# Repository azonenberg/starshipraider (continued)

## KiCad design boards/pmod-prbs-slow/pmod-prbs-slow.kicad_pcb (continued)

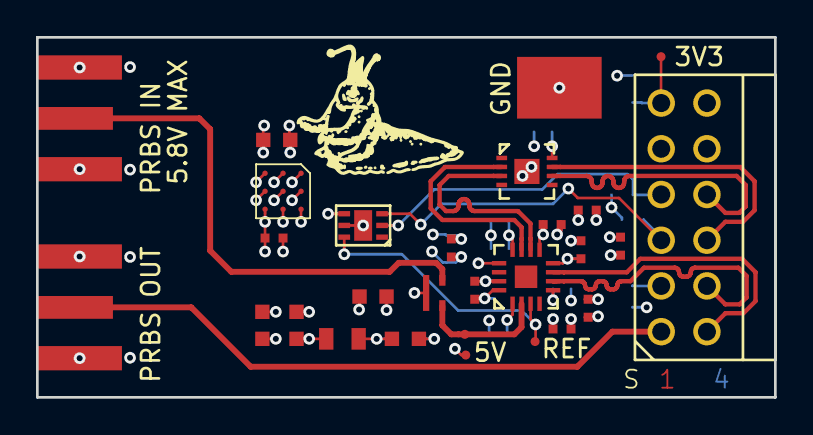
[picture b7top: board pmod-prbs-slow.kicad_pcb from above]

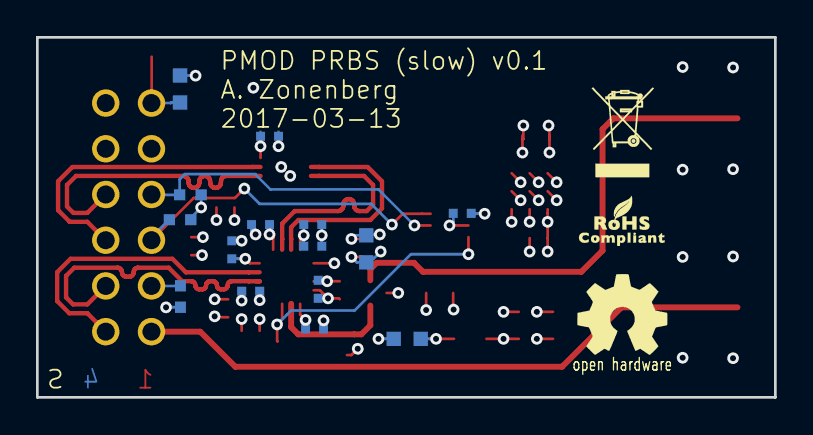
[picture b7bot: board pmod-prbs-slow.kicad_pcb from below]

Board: 4 copper layers, 41.0 x 20.0 mm, 43 parts (15 on the bottom side), 17 nets.

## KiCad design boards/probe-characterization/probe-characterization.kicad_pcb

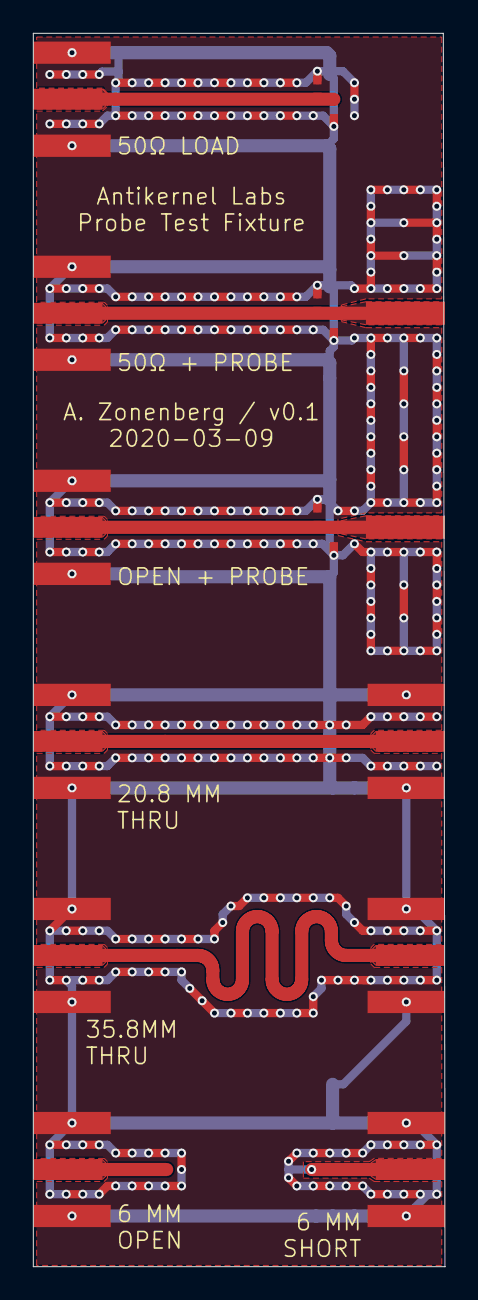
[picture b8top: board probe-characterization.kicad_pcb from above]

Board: 2 copper layers, 25.0 x 74.9 mm, 17 parts (0 on the bottom side), 6 nets.

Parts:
J1, J2, J3, J4, J5, J6, J7, J8, J9: SMA; CONN_SMA_EDGE_SAMTEC_SMA_J_P_H_ST_EM1
J10, J11: PROBE; CONN_MILLMAX_0339_EDGELAUNCH
R1, R2, R4, R5: 100; EIA_0402_RES_NOSILK_FLIPCHIP
R3, R6: DNP; EIA_0402_RES_NOSILK_FLIPCHIP

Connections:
/GND: J1.2, J2.2, J3.2, J4.2, J5.2, J6.2, J7.1, J7.2, J8.2, J9.2, R1.2, R2.2, R3.2, R4.2, R5.2, R6.2
unnamed: J1.1, R1.1, R4.1
unnamed: J4.1, J8.1
unnamed: J5.1, J9.1
unnamed: J2.1, J10.1, R2.1, R5.1
unnamed: J3.1, J11.1, R3.1, R6.1
